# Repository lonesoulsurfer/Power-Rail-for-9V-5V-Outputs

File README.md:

Power supply to run my modular synth.  The majority of the modules are run via Arduino Nano which I power via 9V's.  This rail allows me to connect a battery to the power rail to power all of the modules. I charge the battery via a USB C input and battery charging module.  To get the 9V's needed from the battery I run it through a voltage regulator (just a cheap one from Ali Express) to bring up the voltage to 9V.  Then the power is distributed via JST connectors along the rail. I have also included a voltage regulator on the rail to bring the voltage down to 5V's which can be used to also power other modules using 5V's.

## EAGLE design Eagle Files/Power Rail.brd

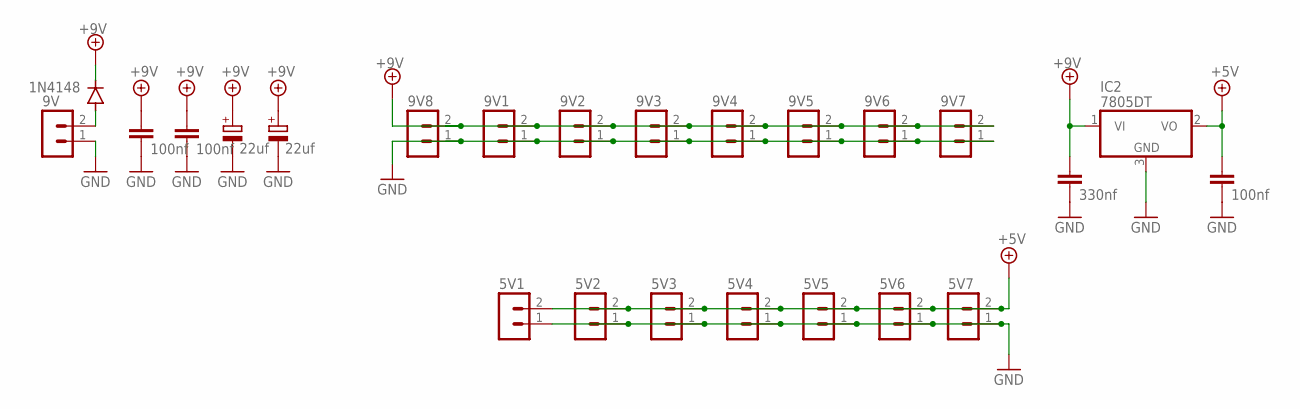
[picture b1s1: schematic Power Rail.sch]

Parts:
5V1, 5V2, 5V3, 5V4, 5V5, 5V6, 5V7, 9V, 9V1, 9V2, 9V3, 9V4, 9V5, 9V6, 9V7, 9V8: B2B-PH-K-S
C1: 330nf; C050-024X044
C2, C5, C6: 100nf; C050-024X044
C3, C4: 22uf; E2-5
D2: 1N4148; DO35-7
IC2: 7805DT; TO252

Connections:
+5V: 5V1.2, 5V2.2, 5V3.2, 5V4.2, 5V5.2, 5V6.2, 5V7.2, C2.1, IC2.2 (VO)
+9V: 9V1.2, 9V2.2, 9V3.2, 9V4.2, 9V5.2, 9V6.2, 9V7.2, 9V8.2, C1.1, C3.+, C4.+, C5.1, C6.1, D2.C, IC2.1 (VI)
GND: 5V1.1, 5V2.1, 5V3.1, 5V4.1, 5V5.1, 5V6.1, 5V7.1, 9V.1, 9V1.1, 9V2.1, 9V3.1, 9V4.1, 9V5.1, 9V6.1, 9V7.1, 9V8.1, C1.2, C2.2, C3.-, C4.-, C5.2, C6.2, IC2.3 (GND)
unnamed: 9V.2, D2.A

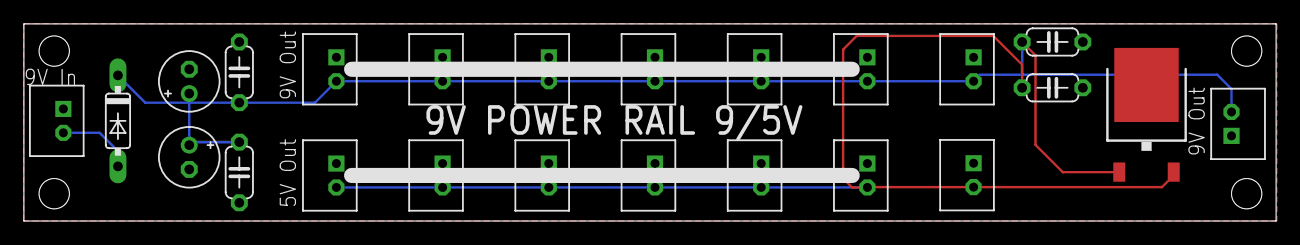
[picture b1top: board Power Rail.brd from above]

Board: 2 copper layers, 104.8 x 16.5 mm, 24 parts (0 on the bottom side), 4 nets.
